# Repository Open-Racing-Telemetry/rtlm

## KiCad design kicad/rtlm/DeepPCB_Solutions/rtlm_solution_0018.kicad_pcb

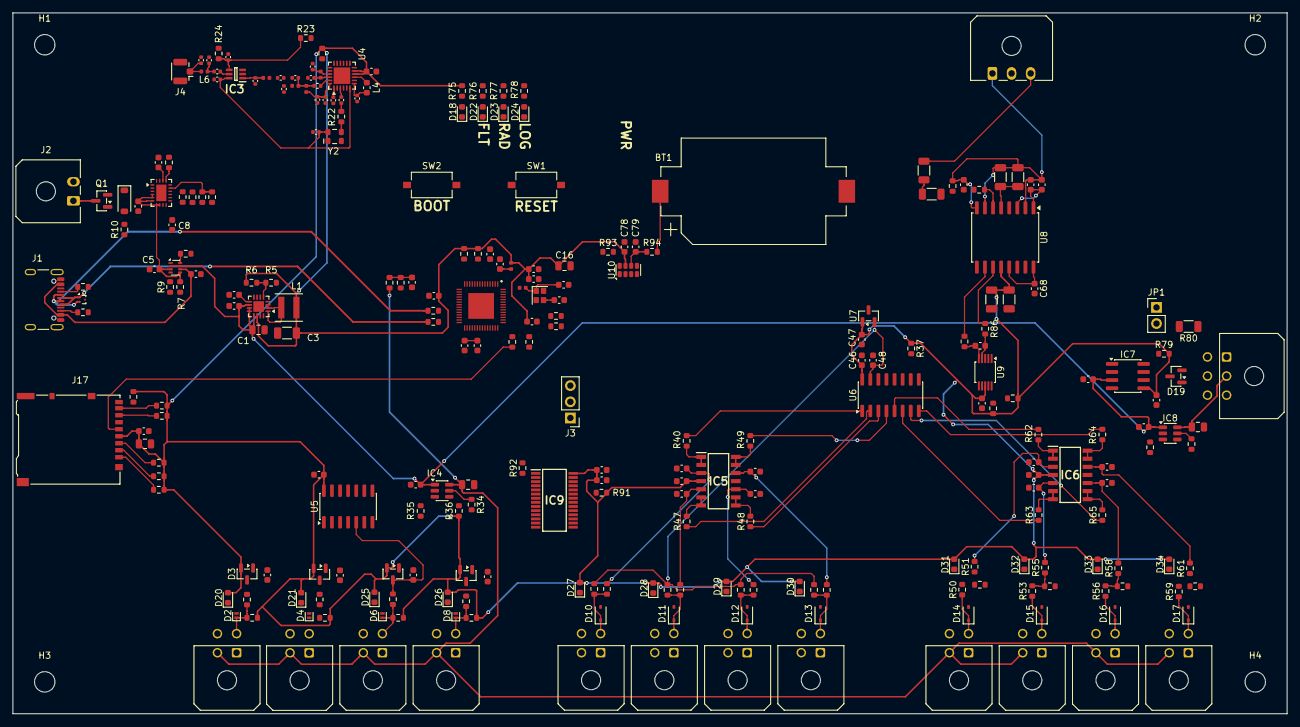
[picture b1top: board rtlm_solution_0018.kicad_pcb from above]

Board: 4 copper layers, 200.0 x 110.0 mm, 265 parts (0 on the bottom side), 172 nets.

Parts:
BT1: CR2032; BatteryHolder_Keystone_1060_1x2032
C1, C16, C44, C60, C65: 10µf; C_0805_2012Metric
C2, C8, C10, C11, C12, C14, C15, C39, C46, C49, C50, C51, C52, C53, C58, C59, C61, C62, C63, C68, C73, C76, C78, C79: 100nf; C_0603_1608Metric
C3: 22µf; C_1206_3216Metric
C4: 3.3nf; C_0603_1608Metric
C5, C6, C9, C13, C17, C18, C38, C42, C48, C66, C69, C77: 1µf; C_0603_1608Metric
C7, C54, C55, C56, C57, C74, C75: 10nf; C_0603_1608Metric
C19, C20: 16pf; C_0603_1608Metric
C21, C23, C26: 100nf; C_0402_1005Metric
C22: 470nf; C_0402_1005Metric
C24: 10pf; C_0402_1005Metric
C25: 1nf; C_0402_1005Metric
C27, C32: 39pf; C_0402_1005Metric
C28: 2.4pf; C_0402_1005Metric
C29, C37: 1.8pf; C_0402_1005Metric
C30, C31: 3.3pf; C_0402_1005Metric
C33: 47nf; C_0402_1005Metric
C34: 47pf; C_0402_1005Metric
C35: 3pf; C_0402_1005Metric
C36: 5.6pf; C_0402_1005Metric
C40, C41, C43, C45, C70: 1nf; C_0603_1608Metric
C47: 470nf; C_0603_1608Metric
C64: 1µf; C_1206_3216Metric
C67, C72: 1nf; C_1206_3216Metric
C71: 100nf; C_1206_3216Metric
D1: BZT52C5V6; D_SOD-123
D2, D4, D6, D8: PESD5V0S1UL; D_SOD-882
D3, D5, D7, D9: BAT54S; SOT-23
D10, D11, D12, D13, D14, D15, D16, D17: PESD5V0L1UA; D_SOD-323
D18, D20, D21, D22, D23, D24, D25, D26, D27, D28, D29, D30, D31, D32, D33, D34: LED; LED_0603_1608Metric
D19: PESD2CAN; SOT-23
H1, H2, H3, H4: MountingHole_3.2mm_M3
IC1: ESP32-S3FN8; QFN40P700X700X90-57N-D
IC2: TPS25940ARVCR; Texas_RVC0020A_WQFN-20-1EP_3x4mm_P0.5mm_EP1.6x2.6mm
IC3: PE4259; SOT65P210X110-6N
IC4, IC8: TPS2553DBVR; SOT-23-6
IC5, IC6: TLV9004IDR; SOIC127P600X175-14N
IC7: TCAN1042HGVDR; SOIC-8_3.9x4.9mm_P1.27mm
IC9: TLC59116IPWR; SOP65P640X120-28N
J1: USB_C_Receptacle_USB2.0_16P; USB_C_Receptacle_GCT_USB4105-xx-A_16P_TopMnt_Horizontal
J2: Conn_01x02; Molex_Micro-Fit_3.0_43650-0200_1x02_P3.00mm_Horizontal
J3: UART_DEBUG_3V3; PinHeader_1x03_P2.54mm_Vertical
J4: LORA_ANT; U.FL_Hirose_U.FL-R-SMT-1_Vertical
J5: PULSE_1; Molex_Micro-Fit_3.0_43045-0400_2x02_P3.00mm_Horizontal
J6: PULSE_2; Molex_Micro-Fit_3.0_43045-0400_2x02_P3.00mm_Horizontal
J7: PULSE_3; Molex_Micro-Fit_3.0_43045-0400_2x02_P3.00mm_Horizontal
J8: PULSE_4; Molex_Micro-Fit_3.0_43045-0400_2x02_P3.00mm_Horizontal
J9: TEMP_1; Molex_Micro-Fit_3.0_43045-0400_2x02_P3.00mm_Horizontal
J10: TEMP_2; Molex_Micro-Fit_3.0_43045-0400_2x02_P3.00mm_Horizontal
J11: TEMP_3; Molex_Micro-Fit_3.0_43045-0400_2x02_P3.00mm_Horizontal
J12: TEMP_4; Molex_Micro-Fit_3.0_43045-0400_2x02_P3.00mm_Horizontal
J13: ANALOG_1; Molex_Micro-Fit_3.0_43045-0400_2x02_P3.00mm_Horizontal
J14: ANALOG_2; Molex_Micro-Fit_3.0_43045-0400_2x02_P3.00mm_Horizontal
J15: ANALOG_3; Molex_Micro-Fit_3.0_43045-0400_2x02_P3.00mm_Horizontal
J16: ANALOG_4; Molex_Micro-Fit_3.0_43045-0400_2x02_P3.00mm_Horizontal
J17: DM3AT-SF-PEJM5; microSD_HC_Hirose_DM3AT-SF-PEJM5
J18: CAN_EXPANSION; Molex_Micro-Fit_3.0_43045-0600_2x03_P3.00mm_Horizontal
J19: BATTERY_VOLTAGE_SENSE_LINE; Molex_Micro-Fit_3.0_43650-0300_1x03_P3.00mm_Horizontal
JP1: CAN_TERM; PinHeader_1x02_P2.54mm_Vertical
L1: 2.2µH; L_Coilcraft_XxL4020
L2: 2nH; L_0402_1005Metric
L3: 24nh; L_0402_1005Metric
L4: 15µh; L_0603_1608Metric
L5: 15nH; L_0402_1005Metric
L6: 9.1nh; L_0402_1005Metric
L7: 2.5nh; L_0402_1005Metric
L8: 4.7nh; L_0402_1005Metric
L9: 47nh; L_0402_1005Metric
Q1: DMP2035U-7; SOT-23
R1, R2: 5.1k; R_0603_1608Metric
R3, R4: 22; R_0603_1608Metric
R5: 24k; R_0603_1608Metric
R6: 75k; R_0603_1608Metric
R7: 30k; R_0603_1608Metric
R8, R10, R35: 100k; R_0603_1608Metric
R9, R13, R15, R16, R17, R18, R19, R21, R36, R37, R38, R41, R43, R45, R52, R54, R57, R60, R67, R68, R69, R70, R71, R72, R74, R79, R91, R93: 10k; R_0603_1608Metric
R11: 59k; R_0603_1608Metric
R12: 44.2k; R_0603_1608Metric
R14: 34.8k; R_0603_1608Metric
R20: 499; R_0603_1608Metric
R22, R23: 220; R_0603_1608Metric
R24, R85: 2.2k; R_0603_1608Metric
R25: 0; R_0402_1005Metric
R26, R29, R31, R33, R75, R76, R77, R78, R90, R94: 1k; R_0603_1608Metric
R27, R28, R30, R32, R39, R42, R44, R46, R51, R55, R58, R61, R88, R89: 4.7k; R_0603_1608Metric
R34, R81: 133k; R_0603_1608Metric
R40, R47, R48, R49, R62, R63, R64, R65: 47; R_0603_1608Metric
R50, R53, R56, R59: 12k; R_0603_1608Metric
R66: 20k; R_0603_1608Metric
R73: 33; R_0603_1608Metric
R80: 120; R_1206_3216Metric
R82, R83: 499k; R_1206_3216Metric
R84: 8.2k; R_0603_1608Metric
R86, R87: 470; R_0603_1608Metric
R92: 1.8k; R_0603_1608Metric
SW1, SW2: SW_Push; SW_Tactile_SPST_NO_Straight_CK_PTS636Sx25SMTRLFS
U1: TPS62130A; VQFN-16-1EP_3x3mm_P0.5mm_EP1.68x1.68mm
U2: TPS2116DRL; SOT-583-8
U3: TPD2EUSB30; Texas_DRT-3
U4: SX1262IMLTRT; QFN-24-1EP_4x4mm_P0.5mm_EP2.6x2.6mm
U5: SN74LVC14ADR; SOIC-14_3.9x8.7mm_P1.27mm
U6: MCP3208-BI/SL; SOIC-16_3.9x9.9mm_P1.27mm
U7: REF3025AIDBZR; SOT-23
U8: AMC3330; SOIC-16W_7.5x10.3mm_P1.27mm
U9: ADS1115IDGS; TSSOP-10_3x3mm_P0.5mm
U10: RV-3028-C7; MicroCrystal_C7_SON-8_1.5x3.2mm_P0.9mm
Y1: 40MHz; Crystal_SMD_SeikoEpson_FA128-4Pin_2.0x1.6mm
Y2: TG2520SMN 32.0000M-MCGNNM3; Oscillator_SMD_SeikoEpson_TG2520SMN-xxx-xxxxxx-4Pin_2.5x2.0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

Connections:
+3.3V: C3.1, C10.2, C11.2, C14.2, C15.2, C16.1, C21.1, C38.1, C39.1, C46.1, C47.1, C50.1, C58.1, C60.1, C61.1, C63.1, C64.2, C67.2, C73.2, C76.1, C77.1, C78.2, D3.2 (K), D5.2 (K), D7.2 (K), D9.2 (K), D20.2 (A), D21.2 (A), D25.2 (A), D26.2 (A), D27.2 (A), D28.2 (A), D29.2 (A), D30.2 (A), D31.2 (A), D32.2 (A), D33.2 (A), D34.2 (A), IC1.20 (VDD3P3_RTC), IC1.46 (VDD3P3_CPU), IC1.55 (VDDA_1), IC1.56 (VDDA_2), IC5.4 (V+), IC6.4 (V+), IC7.5 (VIO), IC9.28 (VCC), J17.4 (VDD), L1.2, L2.1, R6.2, R16.2, R17.2, R21.2, R27.2, R28.2, R30.2, R32.2, R36.2, R37.1, R68.2, R69.2, R70.2, R71.2, R72.2, R74.2, R75.1, R79.2, R88.2, R89.2, R91.2, U1.14 (VOS), U4.1 (VDD_IN), U4.10 (VBAT), U4.11 (VBAT_IO), U5.14 (VCC), U6.16 (Vdd), U7.1 (IN), U8.12 (VDD), U9.8 (VDD), U10.7 (VDD)
/5V_CAN: C65.2, IC8.6 (OUT), J18.2
/5V_PULSE: C44.2, IC4.6 (OUT), J5.2, J6.2, J7.2, J8.2, J13.2, J14.2, J15.2, J16.2, R66.1
/5V_SYS: C1.2, C2.2, C42.2, C62.1, C66.2, IC4.1 (IN), IC7.3 (VCC), IC8.1 (IN), U1.10 (VIN), U1.11 (VIN), U1.12 (VIN), U1.13 (EN), U2.2 (VOUT), U2.7 (VOUT)
/ADC_CS: IC1.23 (GPIO17), R37.2, U6.10 (~CS/SHDN)
/ADC_VREF_2V5: C48.1, R38.1, R41.1, R43.1, R45.1, U6.15 (Vref), U7.2 (OUT)
/ANALOG1_ADC: R62.1, U6.5 (CH4)
/ANALOG1_FILTERED: C54.1, IC6.3 (IN1+), R51.2
/ANALOG1_RAW: D14.1 (K), J13.3, R50.1
/ANALOG2_ADC: R63.1, U6.6 (CH5)
/ANALOG2_FILTERED: C55.1, IC6.5 (IN2+), R55.2
/ANALOG2_RAW: D15.1 (K), J14.3, R53.1
/ANALOG3_ADC: R65.1, U6.7 (CH6)
/ANALOG3_FILTERED: C56.1, IC6.10 (IN3+), R58.2
/ANALOG3_RAW: D16.1 (K), J15.3, R56.1
/ANALOG4_ADC: R64.1, U6.8 (CH7)
/ANALOG4_FILTERED: C57.1, IC6.12 (IN4+), R61.2
/ANALOG4_RAW: D17.1 (K), J16.3, R59.1
/CAN_H: D19.1 (I/O_1), IC7.7 (CANH), J18.3, R80.1
/CAN_L: D19.2 (I/O_2), IC7.6 (CANL), J18.4, JP1.1 (A)
/CAN_PWR_EN: IC1.28 (SPICS1), IC8.3 (EN), R85.1
/CAN_RX: IC1.40 (GPIO35), IC7.4 (RXD)
/CAN_STB: IC1.41 (GPIO36), IC7.8 (STB), R79.1
/CAN_TX: IC1.39 (GPIO34), IC7.1 (TXD)
/ESP_BOOT: IC1.5 (GPIO0), R17.1, SW2.1
/ESP_RESET: C18.2, IC1.4 (CHIP_PU), R16.1, SW1.1
/ESP_U0RXD: IC1.50 (U0RXD), J3.3
/ESP_U0TXD: IC1.49 (U0TXD), R20.2
/ESP_VDD_SPI: C12.1, C13.1, IC1.29 (VDD_SPI)
/ESP_XTAL_N: C19.2, IC1.53 (XTAL_N), Y1.3
/ESP_XTAL_P: IC1.54 (XTAL_P), L3.1
/EXT_5V_POLARITY_OK: C8.2, D1.1 (K), IC2.9 (IN_1), IC2.10 (IN_2), IC2.11 (IN_3), IC2.12 (IN_4), IC2.13 (IN_5), Q1.2 (S), R12.1, R14.2
/EXT_5V_PROTECTED: C5.2, C9.2, IC2.4 (OUT_1), IC2.5 (OUT_2), IC2.6 (OUT_3), IC2.7 (OUT_4), IC2.8 (OUT_5), R7.1, U2.3 (VIN1), U2.5 (MODE)
/EXT_5V_RAW: J2.1, Q1.3 (D)
/HLDO_OUT: C71.2, C72.2, U8.5 (HLDO_OUT)
/I2C_SCL: IC1.36 (SPICLK_N), IC9.26 (SCL), R88.1, U9.10 (SCL), U10.3 (SCL)
/I2C_SDA: IC1.37 (SPICLK_P), IC9.27 (SDA), R89.1, U9.9 (SDA), U10.4 (SDA)
/LED_FAULT: IC1.38 (GPIO33), R76.1
/LED_LOG: IC1.21 (XTAL_32K_P), R78.1
/LED_OUT0: D20.1 (K), IC9.6 (~OUT0)
/LED_OUT1: D21.1 (K), IC9.7 (~OUT1)
/LED_OUT2: D25.1 (K), IC9.8 (~OUT2)
/LED_OUT3: D26.1 (K), IC9.9 (~OUT3)
/LED_OUT4: D27.1 (K), IC9.11 (~OUT4)
/LED_OUT5: D28.1 (K), IC9.12 (~OUT5)
/LED_OUT6: D29.1 (K), IC9.13 (~OUT6)
/LED_OUT7: D30.1 (K), IC9.14 (~OUT7)
/LED_OUT8: D31.1 (K), IC9.15 (~OUT8)
/LED_OUT9: D32.1 (K), IC9.16 (~OUT9)
/LED_OUT10: D33.1 (K), IC9.17 (~OUT10)
/LED_OUT11: D34.1 (K), IC9.18 (~OUT11)
/LED_RADIO: IC1.22 (XTAL_32K_N), R77.1
/LORA_3V0: C23.2, C26.2, IC3.6 (~CTRL_OR_VDD), U4.6 (DIO3), Y2.4 (Vcc)
/LORA_BUSY: IC1.10 (GPIO5), U4.14 (BUSY)
/LORA_CS: IC1.15 (GPIO10), R21.1, U4.19 (NSS)
/LORA_IRQ: IC1.11 (GPIO6), U4.13 (DIO1)
/LORA_MISO: IC1.18 (GPIO13), U4.16 (MISO), U6.12 (Dout)
/LORA_MOSI: IC1.16 (GPIO11), U4.17 (MOSI), U6.11 (Din)
/LORA_RESET: IC1.9 (GPIO4), U4.15 (~RESET)
/LORA_RFI_N: C28.2, L5.1, U4.22 (RFI_N)
/LORA_RFO: R25.1, U4.23 (RFO)
/LORA_SCK: IC1.17 (GPIO12), U4.18 (SCK), U6.13 (CLK)
/LORA_VR_PA: C33.1, C34.1, L9.2, U4.24 (VR_PA)
/LORA_XTA: C24.2, U4.3 (XTA)
/PACK_NEG: C69.1, C70.1, C71.1, C72.1, C74.2, J19.1, R84.1, U8.2 (DCDC_HGND), U8.7 (INN), U8.8 (HGND)
/PACK_POS: J19.3, R82.1
/PACK_V_SENSE: R90.2, U8.6 (INP)
/PULSE1_RAW: D2.1 (K), J5.3, R26.1, R27.1
/PULSE2_RAW: D4.1 (K), J6.3, R28.1, R29.1
/PULSE3_RAW: D6.1 (K), J7.3, R30.1, R31.1
/PULSE4_RAW: D8.1 (K), J8.3, R32.1, R33.1
/PULSE_1: IC1.12 (GPIO7), U5.2
/PULSE_2: IC1.13 (GPIO8), U5.4
/PULSE_3: IC1.14 (GPIO9), U5.6
/PULSE_4: IC1.19 (GPIO14), U5.8
/PULSE_PWR_EN: IC1.6 (GPIO1), IC4.3 (EN), R35.1
/PWR_PRIORITY: R7.2, R8.2, R9.1, U2.4 (PR1)
/RTC_BACKUP: C79.2, R94.1, U10.6 (VBACKUP)
/SD_CLK: J17.5 (CLK), R73.2
/SD_CMD: IC1.44 (MTCK), J17.3 (CMD), R70.1
/SD_D0: IC1.45 (MTDO), J17.7 (DAT0), R71.1
/SD_D1: IC1.47 (MTDI), J17.8 (DAT1), R72.1
/SD_D2: IC1.48 (MTMS), J17.1 (DAT2), R68.1
/SD_D3: IC1.42 (GPIO37), J17.2 (DAT3/CD), R69.1
/SD_DETECT: IC1.27 (GPIO21), J17.9 (DET_B), R74.1
/SENSOR_5V_MON: C59.1, IC1.24 (GPIO18), R66.2, R67.2
/SENSOR_PWR_FAULT: IC1.7 (GPIO2), IC4.4 (~FAULT), IC8.4 (~FAULT), R36.1
/TEMP1_ADC: R40.1, U6.1 (CH0)
/TEMP1_FILTERED: C49.1, IC5.3 (IN1+), R39.2
/TEMP1_RAW: D10.1 (K), J9.3, R38.2, R39.1
/TEMP2_ADC: R47.1, U6.2 (CH1)
/TEMP2_FILTERED: C51.1, IC5.5 (IN2+), R42.2
/TEMP2_RAW: D11.1 (K), J10.3, R41.2, R42.1
/TEMP3_ADC: R48.1, U6.3 (CH2)
/TEMP3_FILTERED: C52.1, IC5.10 (IN3+), R44.2
/TEMP3_RAW: D12.1 (K), J11.3, R43.2, R44.1
/TEMP4_ADC: R49.1, U6.4 (CH3)
/TEMP4_FILTERED: C53.1, IC5.12 (IN4+), R46.2
/TEMP4_RAW: D13.1 (K), J12.3, R45.2, R46.1
/USB_5V: C6.1, J1.A4 (VBUS), J1.A9 (VBUS), J1.B4 (VBUS), J1.B9 (VBUS), U2.6 (VIN2)
/USB_DN: J1.A7 (D-), J1.B7 (D-), R3.1, U3.2 (D-)
/USB_DP: J1.A6 (D+), J1.B6 (D+), R4.1, U3.1 (D+)
/VMON_DCDC_IN: C68.1, U8.13 (LDO_OUT), U8.16 (DCDC_IN)
/VMON_ISO_SUPPLY: C69.2, C70.2, U8.1 (DCDC_OUT), U8.3 (HLDO_IN)
GND: BT1.2 (-), C1.1, C2.1, C3.2, C4.1, C5.1, C6.2, C7.1, C8.1, C9.1, C10.1, C11.1, C12.2, C13.2, C14.1, C15.1, C16.2, C17.1, C18.1, C19.1, C20.1, C21.2, C22.1, C23.1, C25.1, C26.1, C29.1, C30.2, C31.2, C33.2, C34.2, C36.2, C37.2, C38.2, C39.2, C40.2, C41.2, C42.1, C43.2, C44.1, C45.2, C46.2, C47.2, C48.2, C49.2, C50.2, C51.2, C52.2, C53.2, C54.2, C55.2, C56.2, C57.2, C58.2, C59.2, C60.2, C61.2, C62.2, C63.2, C64.1, C65.1, C66.1, C67.1, C68.2, C73.1, C76.2, C77.2, C78.1, C79.1, D2.2 (A), D3.1 (A), D4.2 (A), D5.1 (A), D6.2 (A), D7.1 (A), D8.2 (A), D9.1 (A), D10.2 (A), D11.2 (A), D12.2 (A), D13.2 (A), D14.2 (A), D15.2 (A), D16.2 (A), D17.2 (A), D18.1 (K), D19.3 (I/O_3), D22.1 (K), D23.1 (K), D24.1 (K), IC1.57 (GND), IC2.1 (DEVSLP), IC2.3 (PGTH), IC2.16 (GND), IC2.21 (EPAD), IC3.2 (GND), IC4.2 (GND), IC5.11 (V-), IC6.11 (V-), IC7.2 (GND), IC8.2 (GND), IC9.2 (A0), IC9.3 (A1), IC9.4 (A2), IC9.5 (A3), IC9.10 (GND_1), IC9.19 (GND_2), IC9.24 (GND_3), J1.A1 (GND), J1.A12 (GND), J1.B1 (GND), J1.B12 (GND), J1.SH (SHIELD), J2.2, J3.1, J4.2 (Ext), J5.1, J6.1, J7.1, J8.1, J9.1, J10.1, J11.1, J12.1, J13.1, J14.1, J15.1, J16.1, J17.6 (VSS), J17.10 (DET_A), J17.SH (SHIELD), J18.1, R1.2, R2.2, R5.2, R9.2, R10.2, R11.1, R13.2, R15.2, R18.1, R19.1, R24.1, R34.2, R35.2, R52.2, R54.2, R57.2, R60.2, R67.1, R81.2, R85.2, R92.2, R93.1, SW1.2, SW2.2, U1.6 (GND), U1.7 (FSW), U1.8 (DEF), U1.15 (GND), U1.16 (GND), U1.17 (GND), U2.1 (GND), U3.3 (GND), U4.2 (GND), U4.5 (GND), U4.8 (GND), U4.20 (GND), U4.25 (GND), U5.7 (GND), U5.11, U5.13, U6.9 (DGND), U6.14 (AGND), U7.3 (GND), U8.9 (GND), U8.15 (DCDC_GND), U9.1 (ADDR), U9.3 (GND), U9.6 (AIN2), U9.7 (AIN3), U10.5 (VSS), Y1.2 (G), Y1.4 (G), Y2.2 (GND)
unnamed: BT1.1 (+), R94.2
unnamed: C20.2, L3.2, Y1.1
unnamed: C24.1, R22.2
unnamed: C27.1, C31.1, L6.2
unnamed: C32.1, C35.2, C36.1, L7.2
unnamed: C32.2, L8.1
unnamed: C35.1, L7.1, L9.1, R25.2
unnamed: C74.1, R83.2, R84.2, R90.1
unnamed: D1.2 (A), Q1.1 (G), R10.1
unnamed: C40.1, D3.3 (COM), R26.2, U5.1
unnamed: C41.1, D5.3 (COM), R29.2, U5.3
unnamed: C43.1, D7.3 (COM), R31.2, U5.5
unnamed: C45.1, D9.3 (COM), R33.2, U5.9
unnamed: D18.2 (A), R75.2
unnamed: D22.2 (A), R76.2
unnamed: D23.2 (A), R77.2
unnamed: D24.2 (A), R78.2
unnamed: IC1.25 (GPIO19), R3.2
unnamed: IC1.26 (GPIO20), R4.2
unnamed: IC1.43 (GPIO38), R73.1
unnamed: IC1.51 (GPIO45), R19.2
unnamed: IC1.52 (GPIO46), R18.2
unnamed: C17.2, IC1.2 (VDD3P3_1), IC1.3 (VDD3P3_2), L2.2
unnamed: C7.2, IC2.18 (DVDT)
unnamed: IC2.14 (EN), R14.1, R15.1
unnamed: IC2.17 (ILIM), R11.2
unnamed: IC2.15 (OVP), R12.2, R13.1
unnamed: C25.2, IC3.4 (CTRL), R23.1, R24.2
unnamed: C37.1, IC3.1 (RF1), L8.2
unnamed: C28.1, IC3.3 (RF2)
unnamed: C27.2, IC3.5 (RFC)
unnamed: IC4.5 (ILIM), R34.1
unnamed: IC5.1 (OUT1), IC5.2 (IN1-), R40.2
unnamed: IC5.6 (IN2-), IC5.7 (OUT2), R47.2
unnamed: IC5.8 (OUT3), IC5.9 (IN3-), R48.2
unnamed: IC5.13 (IN4-), IC5.14 (OUT4), R49.2
unnamed: IC6.1 (OUT1), IC6.2 (IN1-), R62.2
unnamed: IC6.6 (IN2-), IC6.7 (OUT2), R63.2
unnamed: IC6.8 (OUT3), IC6.9 (IN3-), R65.2
unnamed: IC6.13 (IN4-), IC6.14 (OUT4), R64.2
unnamed: IC8.5 (ILIM), R81.1
unnamed: IC9.1 (REXT), R92.1
unnamed: IC9.25 (~RESET), R91.1
unnamed: J1.A5 (CC1), R1.1
unnamed: J1.B5 (CC2), R2.1
unnamed: J3.2, R20.1
unnamed: C30.1, J4.1 (In), L6.1
unnamed: JP1.2 (B), R80.2
unnamed: L1.1, U1.1 (SW), U1.2 (SW), U1.3 (SW)
unnamed: R50.2, R51.1, R52.1
unnamed: R53.2, R54.1, R55.1
unnamed: R56.2, R57.1, R58.1
unnamed: R59.2, R60.1, R61.1
unnamed: R82.2, R83.1
unnamed: R5.1, R6.1, U1.5 (FB)
unnamed: C4.2, U1.9 (SS/TR)
unnamed: R8.1, U2.8 (ST)
unnamed: L4.2, U4.9 (DCC_SW)
unnamed: R23.2, U4.12 (DIO2)
unnamed: C29.2, L5.2, U4.21 (RFI_P)
unnamed: C22.2, L4.1, U4.7 (VREG)
unnamed: R87.1, U8.10 (OUTN)
unnamed: R86.1, U8.11 (OUTP)
unnamed: C75.1, R86.2, U9.4 (AIN0)
unnamed: C75.2, R87.2, U9.5 (AIN1)
unnamed: R93.2, U10.8 (EVI)
unnamed: R22.1, Y2.3 (OUT)
